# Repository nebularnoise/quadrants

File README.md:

# Quadrants

Quadrants is a skiff-friendly SMD version of the [Prok Drum Modules](https://www.thonk.co.uk/product-category/manufacturer/prok-modular/).

I love the Prok modules, but the 3-boards sandwich made them too deep to fit in my drum skiff. With this version, the depth is no longer about 40mm, but rather 30mm.

# License

This work is licensed under CC-by-SA 3.0.

It is an adaptation of [Prok-Drums-Hardware](https://github.com/Normalised/Prok-Drums-Hardware), CC-by-SA 3.0 Martin Wood-Mitrovski, a.k.a [@Normalised](https://github.com/Normalised).
Prok Drums is itself an adaptation of [Radio Music](https://github.com/TomWhitwell/RadioMusic), CC-by-SA 3.0 Tom Whitwell, a.k.a. [Music Thing Modular](https://musicthing.co.uk/).

To quote the official Prok Drums page:
> Prok Drums are open hardware, they are a modified version of the Music Thing Modular Radio Music module by Tom Whitwell and have the Creative Commons license CC-BY-SA: Attribution / ShareAlike. If you use any work from this hardware, you should credit Tom Whitwell, and you must republish any changes you make under the same license. The Prok Drums Eagle PCB projects are available under the creative commons license here – [Github Link](https://github.com/Normalised/Prok-Drums-Hardware)

The Quadrants panel uses pictograms derived from the Mutable Instruments Plaits module, licensed under CC-by-SA 3.0. As such, the panel is also licensed under CC-by-SA 3.0.

# Submodule credits
- [4ms/4ms-kicad-lib](https://github.com/4ms/4ms-kicad-lib): Used for some component footprints
  - Thonkiconns
  - Yamaichi SD card holder
  - Alpha 9mm pots
  - rail mounting hole
- [XenGi/teensy.pretty](github.com/XenGi/teensy.pretty): used as inspiration for teensy footprint
- [XenGi/teensy_library](github.com/XenGi/teensy_library): used as inspiration for teensy symbol

# Graphics credit
- Clap icon by [Chathura Kudahetti, LK](https://thenounproject.com/chathura/), released under Public Domain license
- Other pictograms are derived from the Mutable Instruments Plaits module, licensed under CC-by-SA 3.0

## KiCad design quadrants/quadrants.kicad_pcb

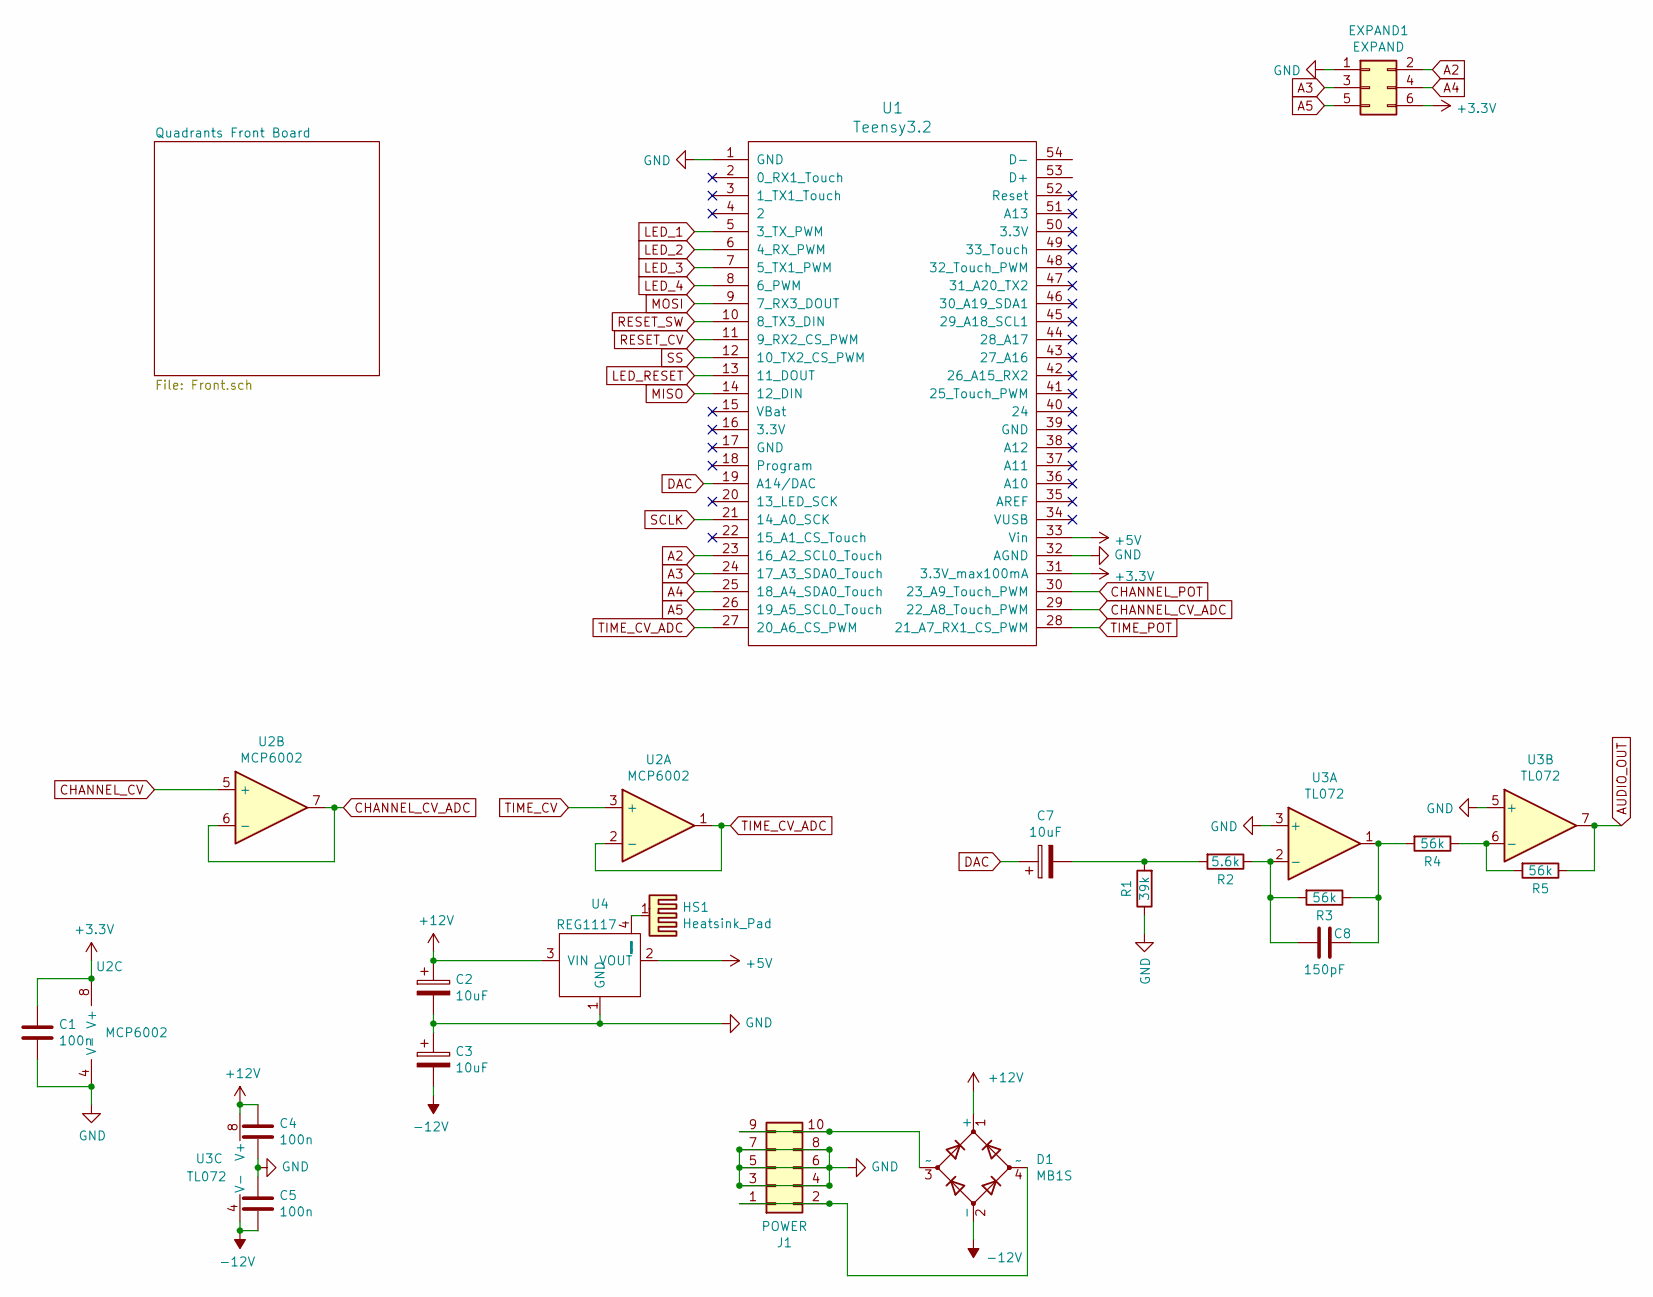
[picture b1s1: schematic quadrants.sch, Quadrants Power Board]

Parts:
C1, C4, C5: 100n; C_0603_1608Metric
C2, C3, C7: 10uF; CP_Elec_5x5.9
C8: 150pF; C_0603_1608Metric
D1: MB1S; SOIC-4-POWER
EXPAND1: EXPAND; PinHeader_2x03_P2.54mm_Vertical
HS1: Heatsink_Pad
J1: POWER; PinHeader_2x05_P2.54mm_Vertical
R1: 39k; R_0603_1608Metric
R2: 5.6k; R_0603_1608Metric
R3, R4, R5: 56k; R_0603_1608Metric
U1: Teensy3.2; Teensy30_31_32_LC
U2: MCP6002; MSOP-8_3x3mm_P0.65mm
U3: TL072; TSSOP-8_4.4x3mm_P0.65mm
U4: REG1117; SOT-223

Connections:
+5V: U1.33 (Vin), U4.2 (VOUT)
+12V: C2.1, C4.1, D1.1 (+), U3.8 (V+), U4.3 (VIN)
-12V: C3.2, C5.2, D1.2 (-), U3.4 (V-)
A2: EXPAND1.2, U1.23 (16_A2_SCL0_Touch)
A3: EXPAND1.3, U1.24 (17_A3_SDA0_Touch)
A4: EXPAND1.4, U1.25 (18_A4_SDA0_Touch)
A5: EXPAND1.5, U1.26 (19_A5_SCL0_Touch)
AUDIO_OUT: R5.1, U3.7; also elsewhere on the board
CHANNEL_CV: U2.5 (+); also elsewhere on the board
CHANNEL_CV_ADC: U1.29 (22_A8_Touch_PWM), U2.6 (-), U2.7
CHANNEL_POT: U1.30 (23_A9_Touch_PWM); also elsewhere on the board
DAC: C7.1, U1.19 (A14/DAC)
GND: C1.2, C2.2, C3.1, C4.2, C5.1, EXPAND1.1, J1.3, J1.4, J1.5, J1.6, J1.7, J1.8, R1.1, U1.1 (GND), U1.32 (AGND), U2.4 (V-), U3.3 (+), U3.5 (+), U4.1 (GND); also elsewhere on the board
LED_1: U1.5 (3_TX_PWM); also elsewhere on the board
LED_2: U1.6 (4_RX_PWM); also elsewhere on the board
LED_3: U1.7 (5_TX1_PWM); also elsewhere on the board
LED_4: U1.8 (6_PWM); also elsewhere on the board
LED_RESET: U1.13 (11_DOUT); also elsewhere on the board
MISO: U1.14 (12_DIN); also elsewhere on the board
MOSI: U1.9 (7_RX3_DOUT); also elsewhere on the board
unnamed: C7.2, R1.2, R2.2
unnamed: C8.1, R2.1, R3.2, U3.2 (-)
unnamed: C8.2, R3.1, R4.2, U3.1
unnamed: D1.3 (~~), J1.9, J1.10
unnamed: D1.4 (~~), J1.1, J1.2
unnamed: HS1.1, U4.4 (HEATSINK)
unnamed: R4.1, R5.2, U3.6 (-)
RESET_CV: U1.11 (9_RX2_CS_PWM); also elsewhere on the board
RESET_SW: U1.10 (8_TX3_DIN); also elsewhere on the board
SCLK: U1.21 (14_A0_SCK); also elsewhere on the board
SS: U1.12 (10_TX2_CS_PWM); also elsewhere on the board
TIME_CV: U2.3 (+); also elsewhere on the board
TIME_CV_ADC: U1.27 (20_A6_CS_PWM), U2.1, U2.2 (-)
TIME_POT: U1.28 (21_A7_RX1_CS_PWM); also elsewhere on the board

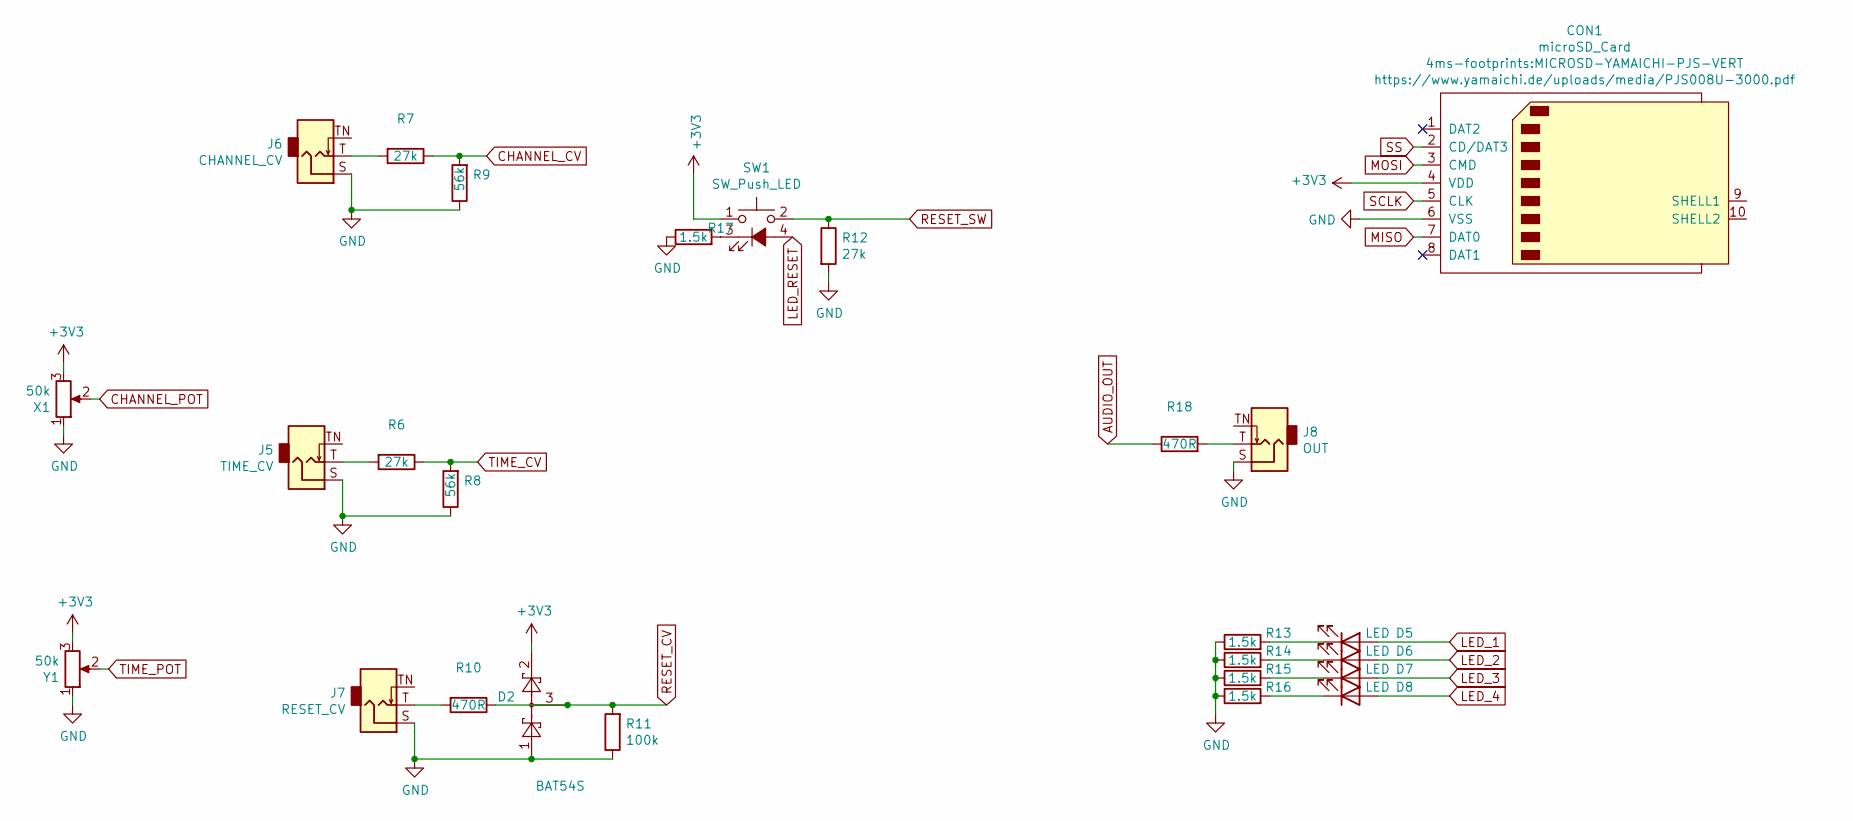
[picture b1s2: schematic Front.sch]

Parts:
CON1: microSD_Card; MICROSD-YAMAICHI-PJS-VERT
D2: BAT54S; SOT-23
D5, D6, D7, D8: LED; LED-3MM-SQUARE-ANODE
J5: TIME_CV; PJ301M-12
J6: CHANNEL_CV; PJ301M-12
J7: RESET_CV; PJ301M-12
J8: OUT; PJ301M-12
R6, R7, R12: 27k; R_0603_1608Metric
R8, R9: 56k; R_0603_1608Metric
R10, R18: 470R; R_0603_1608Metric
R11: 100k; R_0603_1608Metric
R13, R14, R15, R16, R17: 1.5k; R_0603_1608Metric
SW1: SW_Push_LED; KS01BL
X1: 50k; POT-9MM-ALPHA
Y1: 50k; POT-9MM-ALPHA

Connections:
AUDIO_OUT: R18.1; also elsewhere on the board
CHANNEL_CV: R7.1, R9.2; also elsewhere on the board
CHANNEL_POT: X1.2; also elsewhere on the board
GND: CON1.6 (VSS), D2.1, J5.S, J6.S, J7.S, J8.S, R8.1, R9.1, R11.1, R12.2, R13.1, R14.1, R15.1, R16.1, R17.1, X1.1, Y1.1; also elsewhere on the board
LED_1: D5.2 (A); also elsewhere on the board
LED_2: D6.2 (A); also elsewhere on the board
LED_3: D7.2 (A); also elsewhere on the board
LED_4: D8.2 (A); also elsewhere on the board
LED_RESET: SW1.4 (A); also elsewhere on the board
MISO: CON1.7 (DAT0); also elsewhere on the board
MOSI: CON1.3 (CMD); also elsewhere on the board
unnamed: D5.1 (K), R13.2
unnamed: D6.1 (K), R14.2
unnamed: D7.1 (K), R15.2
unnamed: D8.1 (K), R16.2
unnamed: J5.T, R6.2
unnamed: J6.T, R7.2
unnamed: J7.T, R10.2
unnamed: J8.T, R18.2
unnamed: R17.2, SW1.3 (K)
RESET_CV: D2.3, R10.1, R11.2; also elsewhere on the board
RESET_SW: R12.1, SW1.2; also elsewhere on the board
SCLK: CON1.5 (CLK); also elsewhere on the board
SS: CON1.2 (CD/DAT3); also elsewhere on the board
TIME_CV: R6.1, R8.2; also elsewhere on the board
TIME_POT: Y1.2; also elsewhere on the board

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
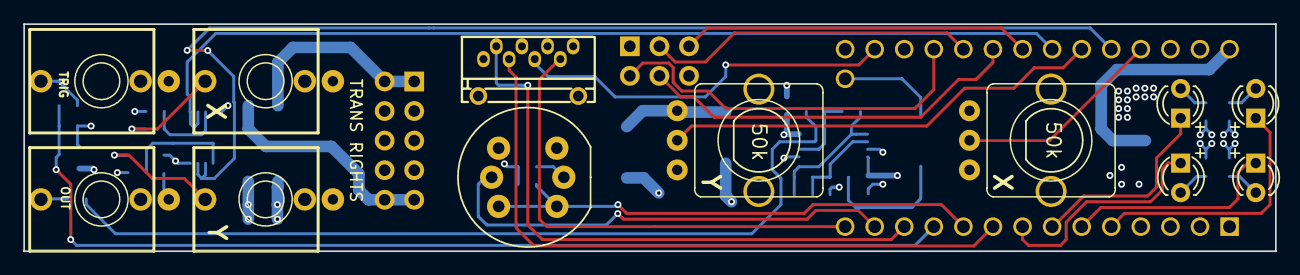
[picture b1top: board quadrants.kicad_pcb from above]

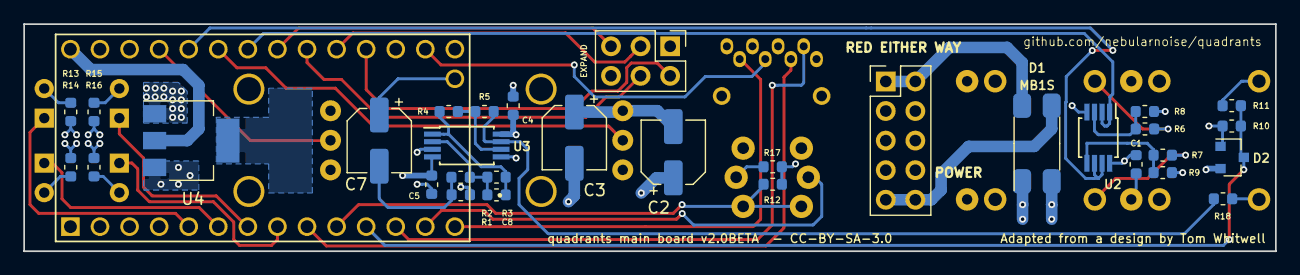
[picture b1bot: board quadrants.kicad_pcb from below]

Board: 4 copper layers, 107.5 x 19.5 mm, 45 parts (33 on the bottom side), 43 nets.

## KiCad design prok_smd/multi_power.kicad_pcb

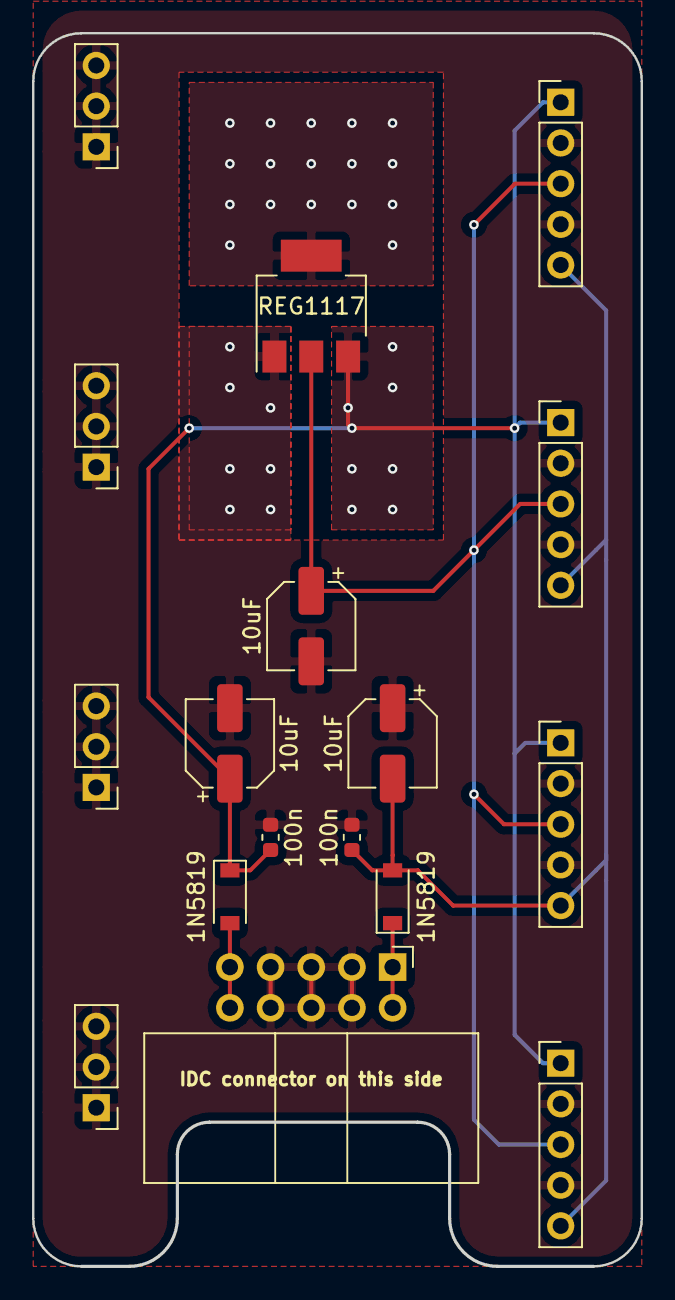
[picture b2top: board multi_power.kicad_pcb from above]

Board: 2 copper layers, 38.0 x 77.0 mm, 17 parts (0 on the bottom side), 6 nets.

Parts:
C1, C2, C5: 10uF; CP_Elec_5x5.9
C3, C4: 100n; C_0603_1608Metric
D1, D2: 1N5819; D_SOD-123
J1, J3, J6, J9: Conn_01x03_Female; PinHeader_1x03_P2.54mm_Vertical
J2, J4, J5, J8: Conn_01x05_Female; PinHeader_1x05_P2.54mm_Vertical
J7: POWER; IDC-Header_2x05_P2.54mm_Horizontal
U1: REG1117; SOT-223

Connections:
+5V: C5.1, J2.3, J4.3, J5.3, J8.3, U1.2
+12V: C1.1, C3.1, D1.1, J2.1, J4.1, J5.1, J8.1, U1.3
-12V: C2.2, C4.2, D2.2, J2.5, J4.5, J5.5, J8.5
GND: C1.2, C2.1, C3.2, C4.1, C5.2, J1.1, J1.2, J1.3, J2.2, J2.4, J3.1, J3.2, J3.3, J4.2, J4.4, J5.2, J5.4, J6.1, J6.2, J6.3, J7.3, J7.4, J7.5, J7.6, J7.7, J7.8, J8.2, J8.4, J9.1, J9.2, J9.3, U1.1
unnamed: D1.2, J7.9, J7.10
unnamed: D2.1, J7.1, J7.2

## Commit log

2019-06-30 :construction: first draft of kicad smd two board version
2019-06-30 :construction: Aligned UI elements to panel specs
2019-07-01 :construction: Locked headers and added mousebites
2019-07-02 :construction: first draft routing
2019-07-02 :sparkles: finished first draft routing. Matched lengths for SD card traces
2019-07-02 :bug: fixed backwards pots
2019-07-02 :sparkles: Fixed switch led
2019-07-03 :recycle: silkscreen cleanup
2019-07-03 :recycle: traces cleanup
2019-07-03 :see_no_evil: :fire: delete and ignore backup files
2019-07-03 :recycle: reorganize files
2019-07-03 :sparkles: :construction: first draft v2 board
2019-07-03 :sparkles: :construction: first draft routing v2
2019-07-05 :sparkles: Silkscreen cleanup
2019-07-12 :sparkles: Clarify silkscreen LEDs, thicken power traces
2019-07-12 :sparkles: Added multi_power board (powers 4 proks)
2019-07-13 :sparkles: Panel (single)
2019-07-13 :sparkles: Panel (x4 kit)
    Valera round for the font
2019-07-13 :lipstick: Panel (x4) changed graphics (plaits style) & changed name ;)
2019-07-16 :lipstick: :sparkles: Gold (soldermask hole) instead of silkscreen
2019-08-09 :bug: Fix LEDs misplacement
    Led pads were placed 2.5mm lower than they should have.
2020-06-21 :recycle: redid power pcb single
2020-06-24 :recycle: rerouted all pcb
    same
    same
2020-06-24 :zap: Added Either way power and more rugged fixations
    same
2020-06-24 :construction: Add some caps to smoothe PWM
2020-06-24 :lipstick: update README
    same
2020-06-28 :recycle: Redid routing
    same
    same
    same
2020-06-29 Removed submodule external/Panelization.pretty
2020-06-30 :truck: :lipstick: Move CV circuitry back, and clean PCB
    same
2020-07-01 :truck: Rename
2020-07-01 :recycle: :truck: Move stuff around, organise
    same
    same
2020-07-08 :lipstick: Add BLM logo
    same
2020-07-08 :bug: Fix panel single (better clearance for LEDs & switch)
    same
2020-07-08 :bug: redid the panel 4 from new panel 1
2020-07-08 :sparkles: panel 5 !!
2020-07-09 :sparkles: update panels
2021-02-19 :construction: prepare 4 layer board layout
2021-02-20 :construction: first draft at 4 layer layout
    same
2021-02-20 :recycle: Clean up silkscreen
2021-02-22 :recycle: Use THT power header !
2021-02-23 :bug: Fix button footprint
2021-08-14 :fire: Remove a few obsolete dimensions (iirc)

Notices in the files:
prok_smd/multi_power.kicad_pcb:
CC by SA Tom Whitwell
quadrants/quadrants.kicad_pcb:
quadrants main board v2.0BETA  - CC-BY-SA-3.0
